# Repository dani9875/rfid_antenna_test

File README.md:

# rfid_antenna_test

Things to write about:
- purpose of antenna matching
- documents and know how utilised
- mistakes made in connection with parameters
- measuring antenna parameters with VNA
- resolution problem
- tuning

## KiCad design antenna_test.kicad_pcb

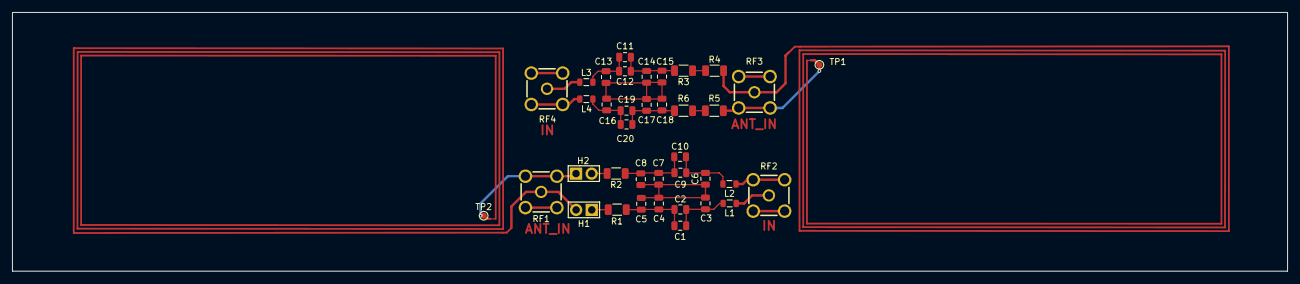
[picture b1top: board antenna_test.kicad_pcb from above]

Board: 2 copper layers, 207.0 x 42.0 mm, 40 parts (0 on the bottom side), 26 nets.

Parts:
AE1, AE2: Antenna_Loop; [Antenna]Custom
C1, C10, C11, C20: C_Small; C_0805_2012Metric
C2, C9, C12, C19: 33pF; C_0805_2012Metric
C3, C6, C13, C16: 100pF; C_0805_2012Metric
C4, C5, C7, C8, C14, C15, C17, C18: 180pF; C_0805_2012Metric
H1, H2: X6511WV-02H-C30D60; [2x1_PIN_HEADER_STR]XKB Connection X6511WV-02H-C60D30
L1, L2, L3, L4: 560nH; L_0805_2012Metric
R1, R2, R3, R6: 3R; R_1206_3216Metric
R4, R5: 0R; R_1206_3216Metric
RF1, RF2, RF3, RF4: BWSMA-KE-Z001; [SMA_CONNECTOR]BAT WIRELESS BWSMA-KE-Z001
TP1, TP2: TestPoint; TestPoint_Pad_D1.0mm

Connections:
unnamed: H1.2, RF1.5
unnamed: H2.1, RF1.1, RF1.2, TP2.1
unnamed: R4.2, RF3.5
unnamed: R5.1, RF3.1, RF3.2, TP1.1
unnamed: C1.1, C2.1, C4.1, C5.1, R1.2
unnamed: C1.2, C2.2, C3.1, L1.2
unnamed: C3.2, C4.2, C5.2, C6.1, C7.1, C8.1
unnamed: C7.2, C8.2, C9.1, C10.1, R2.1
unnamed: C6.2, C9.2, C10.2, L2.2
unnamed: C11.1, C12.1, C14.1, C15.1, R3.2
unnamed: C11.2, C12.2, C13.1, L3.2
unnamed: C13.2, C14.2, C15.2, C16.1, C17.1, C18.1
unnamed: C16.2, C19.2, C20.2, L4.2
unnamed: C17.2, C18.2, C19.1, C20.1, R6.1
unnamed: H1.1, R1.1
unnamed: H2.2, R2.2
unnamed: L1.1, RF2.5
unnamed: L2.1, RF2.3, RF2.4
unnamed: L3.1, RF4.5
unnamed: L4.1, RF4.3, RF4.4
unnamed: R3.1, R4.1
unnamed: R5.2, R6.2
unnamed: RF1.3, RF1.4
unnamed: RF2.1, RF2.2
unnamed: RF3.3, RF3.4
unnamed: RF4.1, RF4.2

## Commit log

2024-06-02 Init HW files
2024-06-02 To be detailed points
2024-10-09 Adding docu folder
